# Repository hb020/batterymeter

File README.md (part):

# Handheld Battery Meter on Attiny series 2 <!-- omit in toc -->

This repository is about a "pen size" (handheld) tool for quick measurement of various types of battery resistances/impedances.

This tool uses 2 different methods for measuring impedance values:

- "standard" AC 1 kHz impedance, as used by many.
- Direct Current Impedance Spectroscopy, extracting the bulk (solution) resistance and the SEI (Solid Electrolyte Interphase) resistance, allowing better insight in both battery ageing and battery safety. Normally this would require a lengthy procedure via EIS (Electrochemical Impedance Spectroscopy) and model fitting. This tool allows to do it fast and easy.

## Contents <!-- omit in toc -->

This document handles the reasoning behind the creation of this tool, the methods used, the software and the hardware.

- [Design restrictions](#design-restrictions)
- [Norms and introduction to measurement techniques used](#norms-and-introduction-to-measurement-techniques-used)
- [Battery Equivalent Circuit Model, Spectrum, and the EIS method](#battery-equivalent-circuit-model-spectrum-and-the-eis-method)
  - [Battery Equivalent Circuit Model](#battery-equivalent-circuit-model)
  - [EIS](#eis)
  - [Tools](#tools)
  - [CN0510](#cn0510)
  - [Model fitting](#model-fitting)
  - [Further information](#further-information)
- [Time Domain / DCIS method](#time-domain--dcis-method)
  - [Non-linear behaviour](#non-linear-behaviour)
  - [Pulse timing](#pulse-timing)
  - [Adaptation to other battery layouts or chemistries](#adaptation-to-other-battery-layouts-or-chemistries)
  - [Ratiometric approach](#ratiometric-approach)
  - [Offset cancelling](#offset-cancelling)
  - [Power line Frequency compensation](#power-line-frequency-compensation)
- [Internal Impedance (AC) measurement](#internal-impedance-ac-measurement)
  - [Current levels and test duration](#current-levels-and-test-duration)
  - [Implementation of the sine wave generation](#implementation-of-the-sine-wave-generation)
  - [AC Analysis method](#ac-analysis-method)
  - [ADC sampling considerations](#adc-sampling-considerations)
  - [Ratiometric approach, Offset cancelling, Power line Frequency compensation](#ratiometric-approach-offset-cancelling-power-line-frequency-compensation)
- [Internal Resistance (DC/IR) measurement](#internal-resistance-dcir-measurement)
- [CPU and Software environment](#cpu-and-software-environment)
- [Construction, Connectors, other hardware](#construction-connectors-other-hardware)
  - [Charging](#charging)
- [Buttons](#buttons)
- [Calibration](#calibration)
- [Remote control, SCPI](#remote-control-scpi)
- [Specifications](#specifications)
  - [Voltage](#voltage)
  - [Resistance](#resistance)
- [Repository contents](#repository-contents)
- [Imperfections, TODO's](#imperfections-todos)

---

## Design restrictions

This tool was designed with the following design restrictions:

- handheld, therefore:
  - small
  - limited controls, ideally by 1 finger while measuring
  - "large enough" screen
  - rechargeable
  - no need to cover a large temperature range
- fast measurement
- easy to use
- for use on regular small batteries. No large capacity car batteries or large UPS batteries, and nothing requiring extreme precision. Therefore:
  - at least 0 to 20 Ω, with, and at least 1 mΩ resolution at the lowest range.
  - at least 1V to 16V, and at least 10mV resolution.
  - at least 3 significant digits.
- precision is more important than accuracy. However, 1% accuracy should be attainable on resistance values. Voltage accuracy is of lower priority, as my DMMs can be used for that, and the voltage is less significant in most cases. Therefore:
  - aim for low noise
  - the accuracy of the measuring techniques should depend on as few as possible variables.
  - calibration must be possible.
- USB charging and USB interface
- hand assembly and hand soldering. For me, that means:
  - no BGA or QFN, as I don't have a reflow oven and am too much of a cheapskate to order stencils for the 1 or 2 PCBs I'll make.
  - 0805 components and VSSOP/MSOP 0.5mm pitch are the low limits
  - as a side effect, I can now freely use both sides of the PCB because I don't have to care about warping or components falling off the other side while soldering with hot air.
- using components that I can find in this period of component shortage. This means that sometimes there might be cheaper or better components, they were just not available when I selected them.
- using an Attiny series 2 CPU, because I wanted to try that out and it looked just capable enough. I really would have liked to use the RP2040, but it is not hand solderable enough. Maybe later.
- capable of using the probes that come with the YR1035+, as I also have that tool, and like the connector/probe ease of use/availability. It will also allow me to have easier comparisons.

## Norms and introduction to measurement techniques used

Battery impedance is a complicated subject. A battery does not have <u>one</u> impedance, and even if you get a number, it can mean many things. Also, the battery impedance depends on a lot of different things, like state of charge (SoC), state of health (SoH), temperature, and of course the measurement method. Therefore, various norms exist for measuring the various resistances and impedances of the different battery types. Some of them are:

- IEC 61951-1: NiCd
- IEC 61951-2: NiMH
- IEC 62660-1/2: Li-Ion
- IEC 61960-4: Lithium coin cells

Outside of these norms, various other test methods have arisen lately. Below is an explanation of the different methods I investigated.

---

## Battery Equivalent Circuit Model, Spectrum, and the EIS method

### Battery Equivalent Circuit Model

Various models of battery impedance exist, depending on the chemistry. For Li-Ion cells, the "Combined Randle and Warburg Circuit Model" is often cited as fairly complete, and, with some variations, also applicable to some other chemistries.

*Equivalent circuit model of a Li-Ion battery half-cell system, and nyquist plot of a frequency sweep.*
([source](https://www.jecst.org/upload/pdf/jecst-2019-00528.pdf))

*Nyquist plot, related to Li-Ion cell chemical processes.*
([source](https://www.analog.com/en/design-center/reference-designs/circuits-from-the-lab/CN0510.html))

### EIS

The EIS (Electrochemical Impedance Spectroscopy) method allows one to get a good view of the various components of the battery impedance. With this method an AC load of varying frequency is imposed on the battery, and the voltage swing over the battery is measured. The frequency sweep can go from the millihertz into the megahertz range, and can be used to generate a Nyquist plot like shown above.

Through model fitting, the values of the individual components in the model can than be determined.

For Li-Ion, the values of these components can be used as indicators.

- R<sub>b</sub> (aka R<sub>s</sub> or R<sub>Ω</sub> in other literature) = Bulk (or Solution) resistance. Increases when the battery ages.
- R<sub>SEI</sub> = Solid Electrolyte Interphase resistance. Is an indication of battery safety: it increases for example when the battery has been overcharged.
- R<sub>ct</sub> = Charge Transfer resistance. Increases when the battery is discharged, and when the temperature is lower. At a stable temperature and SoC, it is also a very good indication of battery health.

As an example, experimental results on Li-Ion batteries show that when the battery capacity drops from 3100 mAh to 2600 mAh due to ageing, the value of R<sub>b</sub> rises from 44 mΩ to 51 mΩ, the value of R<sub>SEI</sub> remains between 6 mΩ and 7 mΩ, and the value of R<sub>ct</sub> rises from 6 mΩ to 20 mΩ.

In spite of the insights EIS can give, it has a couple of drawbacks:

- The values are strongly dependent on the battery chemistry and construction details.
- Interpretation can be complicated.
- The data is too complex to show on a small screen.
- A full EIS test generally takes significant time

As a result, this method is very interesting, but unsuited for implementation in a handheld tool.

Fast measurement of full impedance spectra is possible via the use of multi-sine methods, or via time domain methods. More about this later on.

### Tools

Few "small lab" tools exist that support EIS. Examples are the [Biologic Potentiostat](https://www.biologic.net/product_category/potentiostats-galvanostats/), [Hioki IM3590 and BT4560](https://www.hioki.com/download/37483), or the [BK Precision BA8100](https://www.bkprecision.com/products/electrical-battery-testers/BA8100), all costing several thousands of Euros. But one can already get an idea about EIS via the CN0510 circuit, for a significantly lower budget:

### CN0510

An implementation example of a tool is [CN0510 from analog.com](https://www.analog.com/en/design-center/reference-designs/circuits-from-the-lab/CN0510.html). It allows EIS measurements on various types of batteries. Note however that the signal handling board (EVAL-AD5941BATZ), by default, is only usable in the frequency range of about 4Hz - 5Khz. Outside of that, the accuracy is degraded, and below 1Hz, the noise of the input circuitry gets quite noticeable (1/f noise). With the following minor modifications, 0.5Hz - 5kHz can be made possible though:

- add U4 (otherwise the first couple of seconds of measurements are totally off)
- change C5, C6, C36, C37, C38, C39 from 2.2uF to 10uF.
- change R18, R19, R2, R3, R4, R5 from 2Meg to 10Meg.

### Model fitting

For the impedance analysis and the model fitting, several software packages exist, like [ZView](https://www.scribner.com/software/) or [impedance.py](https://github.com/ECSHackWeek/impedance.py). See the [/EISMeasurements](/EISMeasurements) directory in this repository for some fitting tests with both of these tools.

### Further information

For more information on EIS and alternative methods, see for example <https://www.gamry.com/application-notes/EIS/basics-of-electrochemical-impedance-spectroscopy/> or <https://doi.org/10.1016/j.jpowsour.2020.228742>.

Note that EIS is used in a lot of fields, not only for batteries. However, research on batteries has gotten a significant boost lately with the widespread arrival of electric cars.

---

## Time Domain / DCIS method

As mentioned above, EIS frequency domain analysis is not only complicated, but also lengthy. Time domain analysis methods have come up lately that allow acceptable approximations to the results that can be obtained via EIS. One of the approaches is called DCIS (Direct Current Impedance Spectroscopy), which is described here: <https://www.mdpi.com/1996-1073/14/15/4396/htm>

The idea behind DCIS (and other time domain methods) is that when one exposes the battery to current pulses, the voltage relaxation times give away details of the different RC components in the battery model. Care must be taken to exclude non linear behaviour and to tune the current pulses in such a way that the correct components can be derived easily.

### Non-linear behaviour

One key phrase:

> In the battery model, when the polarization potential change |∆ϕ| caused by an external signal is less than 10 mV and the signal time is short enough, the effect of concentration polarization (Zd in battery model) can be ignored.

I therefore need to keep the test currents low, and the pulses short. Both requirements perfectly fit my tool's design requirements.

### Pulse timing

In regular Li-Ion batteries, the various components show at various frequencies:

- R<sub>b</sub>: > 1kHz
- R<sub>SEI</sub> (and CPE<sub>SEI</sub>): > 1Hz, < 1kHz
- R<sub>ct</sub> (and CPE<sub>electrode</sub> and W): < 1Hz

The approach is that for every individual component, 1 specific timed constant current pulse will be used. The width of the pulse is about 5 * RC time of the component. That gives:

- for R<sub>b</sub>: T<sub>1</sub> = 0.25ms
- for R<sub>SEI</sub>: T<sub>2</sub> = 10ms
- for R<sub>ct</sub>: T<sub>3</sub> = 400ms

The pulses are spaced out by a small relaxation time. The voltage drop over the battery is measured at the end of each current pulse, and the battery resistance at that point in time is calculated:

- for T<sub>1</sub>: V<sub>drop</sub> / I<sub>pulse</sub> = R<sub>b</sub>
- for T<sub>2</sub>: V<sub>drop</sub> / I<sub>pulse</sub> = R<sub>b</sub> + R<sub>SEI</sub>
- for T<sub>3</sub>: V<sub>drop</sub> / I<sub>pulse</sub> = R<sub>b</sub> + R<sub>SEI</sub> + R<sub>ct</sub>

Unfortunately, I will want to do multiple measurements to drown out noise and do power line frequency compensation. That makes T<sub>3</sub> unsuited for my tool, and I must limit myself to  R<sub>b</sub> and R<sub>SEI</sub>.

### Adaptation to other battery layouts or chemistries

The timings mentioned above are suitable for your average Li-Ion 18650 cell. If you want to use the DCIS method on other battery layouts or chemistries, you can adapt the timings via SCPI commands (see `CAL:T(1|2|PAUSE) {uint16}` below).

### Ratiometric approach

The current pulse is sent through the battery, that is placed in series with a known resistor.
The battery resistance is deducted from the relation between the voltage fluctuation over the known resistor and the voltage fluctuation over the battery. Hence, there is no need for a known current source, nor a known voltage reference.

With U<sub>batt</sub> as the voltage drop over the battery, U<sub>ref</sub> the voltage over the reference resistor, and R<sub>ref</sub> the reference resistor: R<sub>batt</sub> = R<sub>ref</sub> * (U<sub>batt</sub>/U<sub>ref</sub>).

Since U<sub>batt</sub> and U<sub>ref</sub> are so small, they are amplified by an AC coupled low noise instrumentation amplifier. The output signal is fed into the differential ADC of the processor. In order to avoid amplification differences and other signal path differences, multiplexing via a common measurement circuit is used. An input switch allows switching between the battery and the reference resistor.

The frequency cut-off point of the high-pass filter at the input of the instrumentation amplifier is well below the frequencies used in the measurements.

### Offset cancelling

The (potentially large) DC offset at the entry of the circuit is cancelled at the start of the measurements, by a low impedance short of the signal to VCC/2. The short is applied for as long is needed, and stopped when the processor sees a close to 0V differential signal on the ADC.

### Power line Frequency compensation

In order to reduce the noise and the influence of the power line frequency, multiple samples are taken, and the results are averaged. The timing of the samples is adapted to the configured power line frequency: an identical number of samples is taken for each opposing polarity of the power line signal.

The software allows setting of the power line frequency (50 or 60) via SCPI commands.

---

## Internal Impedance (AC) measurement

This is the industry standard AC 1kHz test. A small 1kHz current (ideally sine wave) is applied to the battery, and the AC voltage at the battery is measured. The impedance is then deducted from the current and the voltage.
This method is widespread, low power, and fast, so I can include it in my tool.

### Current levels and test duration

The maximum voltage swing allowed depends on the battery type, as above certain levels, the values would be skewed by other factors. For NiCd, that limit is about 20mV, and for Lithium chemistries, 10mV seems to be indicated. As a result, I do not set a test specific current, but adapt the test current to the selected range.

The "correct" duration of the test varies. EC 61951-1 for example states that the test duration must be 1 to 5 seconds, but that is not handy for fast manual use. A test duration of 100ms suffices normally.

### Implementation of the sine wave generation

The CPU I chose does not have a sine wave generator. It does have PWM, but making a sine wave with that was hard to do while running the ADC. As a result, I generate a 1kHz square wave on CPU, and do the transformation to a sine wave with an analog phase-shift circuit. That signal is then, after some amplification and level shifting, fed into a voltage controlled current sink.

### AC Analysis method

Instead of a full fledged FFT/DFT, Goertzel's Algorithm is used. It is essentially a mathematical bandpass filter that gives a magnitude (and phase) reading. It is especially suited as I generate the 1kHz tone myself and can sync the ADC sampling to that tone generation. As a result, it is very light on resources: I can do the calculations while sampling, and do not need large memory buffers.

About the configuration of Goertzel:

- nr_of_samples (N) should be as high as possible:
  - sample_rate/N is bin width.
  - more samples therefore gives more noise suppression
- Target frequencies must be integer multiples of sample_rate/N

Some of the inspirations:

- <https://www.embedded.com/the-goertzel-algorithm/>
- <https://fr.mathworks.com/matlabcentral/answers/?language=fr%2Cen&search_origin=ans_browse&term=goertzel>

### ADC sampling considerations

The CPU having limited RAM, I prefer to do the tone generation, ADC sampling and AC analysis all in sync, run-time. I do not sample and analyse later, as that would take too much RAM. It also gives me the possibility to make the sampling as long as I want, increasing noise suppression. It however requires an optimised ADC loop, so I go outside of megaTinyCore's analogRead() function.

As I have low noise pre-amps, I do not use the PGA: I set gain 0.

The trigger generator is TCA0, the most capable of the timers on the CPU, and I trigger the ADC sampling via the Event system (ADC_START_EVENT_TRIGGER_gc and USERADC0START). During sampling, I generate the 1kHz square wave in code, and do the Goertzel calculations.
Tests have shown that at a 10kHz trigger signal, I have about 20us CPU time left per sample. 12kHz would not be possible, unless I raise the ADC clock rate. Maybe also CCL could help, but I haven't looked.

Interrupts are only used for error conditions on the ADC. Other interrupt sources, like the time library, are disabled, as it would provoke jitter or overruns.

As this is time critical code, debugging support is available in code, via USEREVSYSEVOUTC for example.

I do not use tone(), as that is interrupt driven.

### Ratiometric approach, Offset cancelling, Power line Frequency compensation

A sine wave of 1 kHz is sent through the battery, that is placed in series with a known resistor.
The battery resistance is deducted from the relation between the AC voltage over the known resistor and the AC voltage over the battery. Hence, there is no need for a known current source, nor a known voltage reference.

For more details, see the chapter on "Ratiometric approach" in the description of the DCIS method.

Also here, DC offset cancelling and power line frequency compensation is used. See the related chapters in the description of the DCIS method.

---

## Internal Resistance (DC/IR) measurement

This method is frequently encountered, because it is very simple. It is in essence a DC measurement technique.

> The cell shall be discharged at a constant current of value I<sub>1</sub>. At the end of a discharge period of T<sub>1</sub> s, the voltage U<sub>1</sub> during discharge shall be measured and recorded. The discharge current shall then be immediately increased to a constant value of I<sub>2</sub>, and the corresponding voltage U<sub>2</sub> during discharge shall be measured and recorded again at the end of a discharge period of T<sub>2</sub> s.

Therefore: R<sub>dc</sub> = (U<sub>1</sub> - U<sub>2</sub>)/(I<sub>2</sub> - I<sub>1</sub>)

The currents I<sub>1</sub> and I<sub>2</sub>, and the times T<sub>1</sub> and T<sub>2</sub> depend on the type and capacity of the battery. Example: For NiCd, I<sub>1</sub> is normally between 0.2 and 1 times the C value in Amps, I<sub>2</sub> = 10 * I<sub>1</sub>, T<sub>1</sub> = 10, T<sub>2</sub> = 3. For Lead Acid batteries, the currents can become even larger.

Those large currents, and the accompanying dissipation, make it unsuited for integration in a small handheld tool. Also, because this is such a crude method, abstracting most of the battery model, I am not using this method.

---

## CPU and Software environment

- Arduino IDE (unfortunately. platformIO was not very mature at the time of creation: board support had just arrived.)
- megaTinyCore
- CPU: Attiny 3266-SU (SOIC300, non automotive, 32kB Flash, 3kB RAM, 256B EEPROM)
- Display (SSD1306) via Tiny4kOLED (not SSD1306_minimal, as that is less maintained)
- SparkFun_PCA9536_Arduino_Library
- a modified and local version of vrekrer's scpi_parser

Please note that the flash memory is close to the limit: it is 97% full.

## Construction, Connectors, other hardware

The case chosen is a Hammond 1593DBK. That case comes with flat and curved front/back panels. Use the flat one for the back.

The nose cone is 3D printed, see the [nose cone STEP file](/freecad/noseCone.STEP). The holes for the pins may be too small, I had to drill them out.

The pogo pins in the nose cone are regular R100-1W sockets, with P100-B1 pogo pins. For images and dimensions, see the `pogo-*` files in the [/img](/img) folder.

The probe connector at the back is a "avionics" XS10 4P male connector, the same as on the YR1035+. This connector accepts regular YR1035+ compatible 4W probes, or in conjunction with the nose pogo pins, a custom made - probe (just half of the regular 4W probe). The nose pogo pins are directly connected to the + pins on the XS10 connector. As a result, one can also connect a 4W rig:

The serial connector/charge plug is a USB micro B. I should have chosen USB-C, but I still had a lot of USB micro B connectors.

The navigation switch is a SLLB510100 from Alps Alpine. You probably need some glue to fix it on the PCB, as the "fixing" tabs on the side are very/too small.

The reference resistors are all used in a 4W (kelvin) setup, either through the use of 4W resistors, or in a "poor man's" way, via the PCB layout:

.

All components on the board are specified in the kicad files. The choice of components is, as can be expected, influenced by the component shortage during 2021-2022.

The input circuitry is protected against reverse polarity and moderate overvoltage.

### Charging

If a rechargeable battery is used, the USB charges the battery via trickle charging at about 0.05C for your average 850mAh NiMh AAA battery. This charge current is so little that charging while ON is not possible. Therefore: Charge while OFF.

## Buttons

ON: short press button at the back.

OFF: long press button at the back, or via software control.

Switch between AC and DCIS measurement, or leave remote control: press the navigation switch.

Change range: via left/right of the navigation switch. The 'Auto' range is at both ends.

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
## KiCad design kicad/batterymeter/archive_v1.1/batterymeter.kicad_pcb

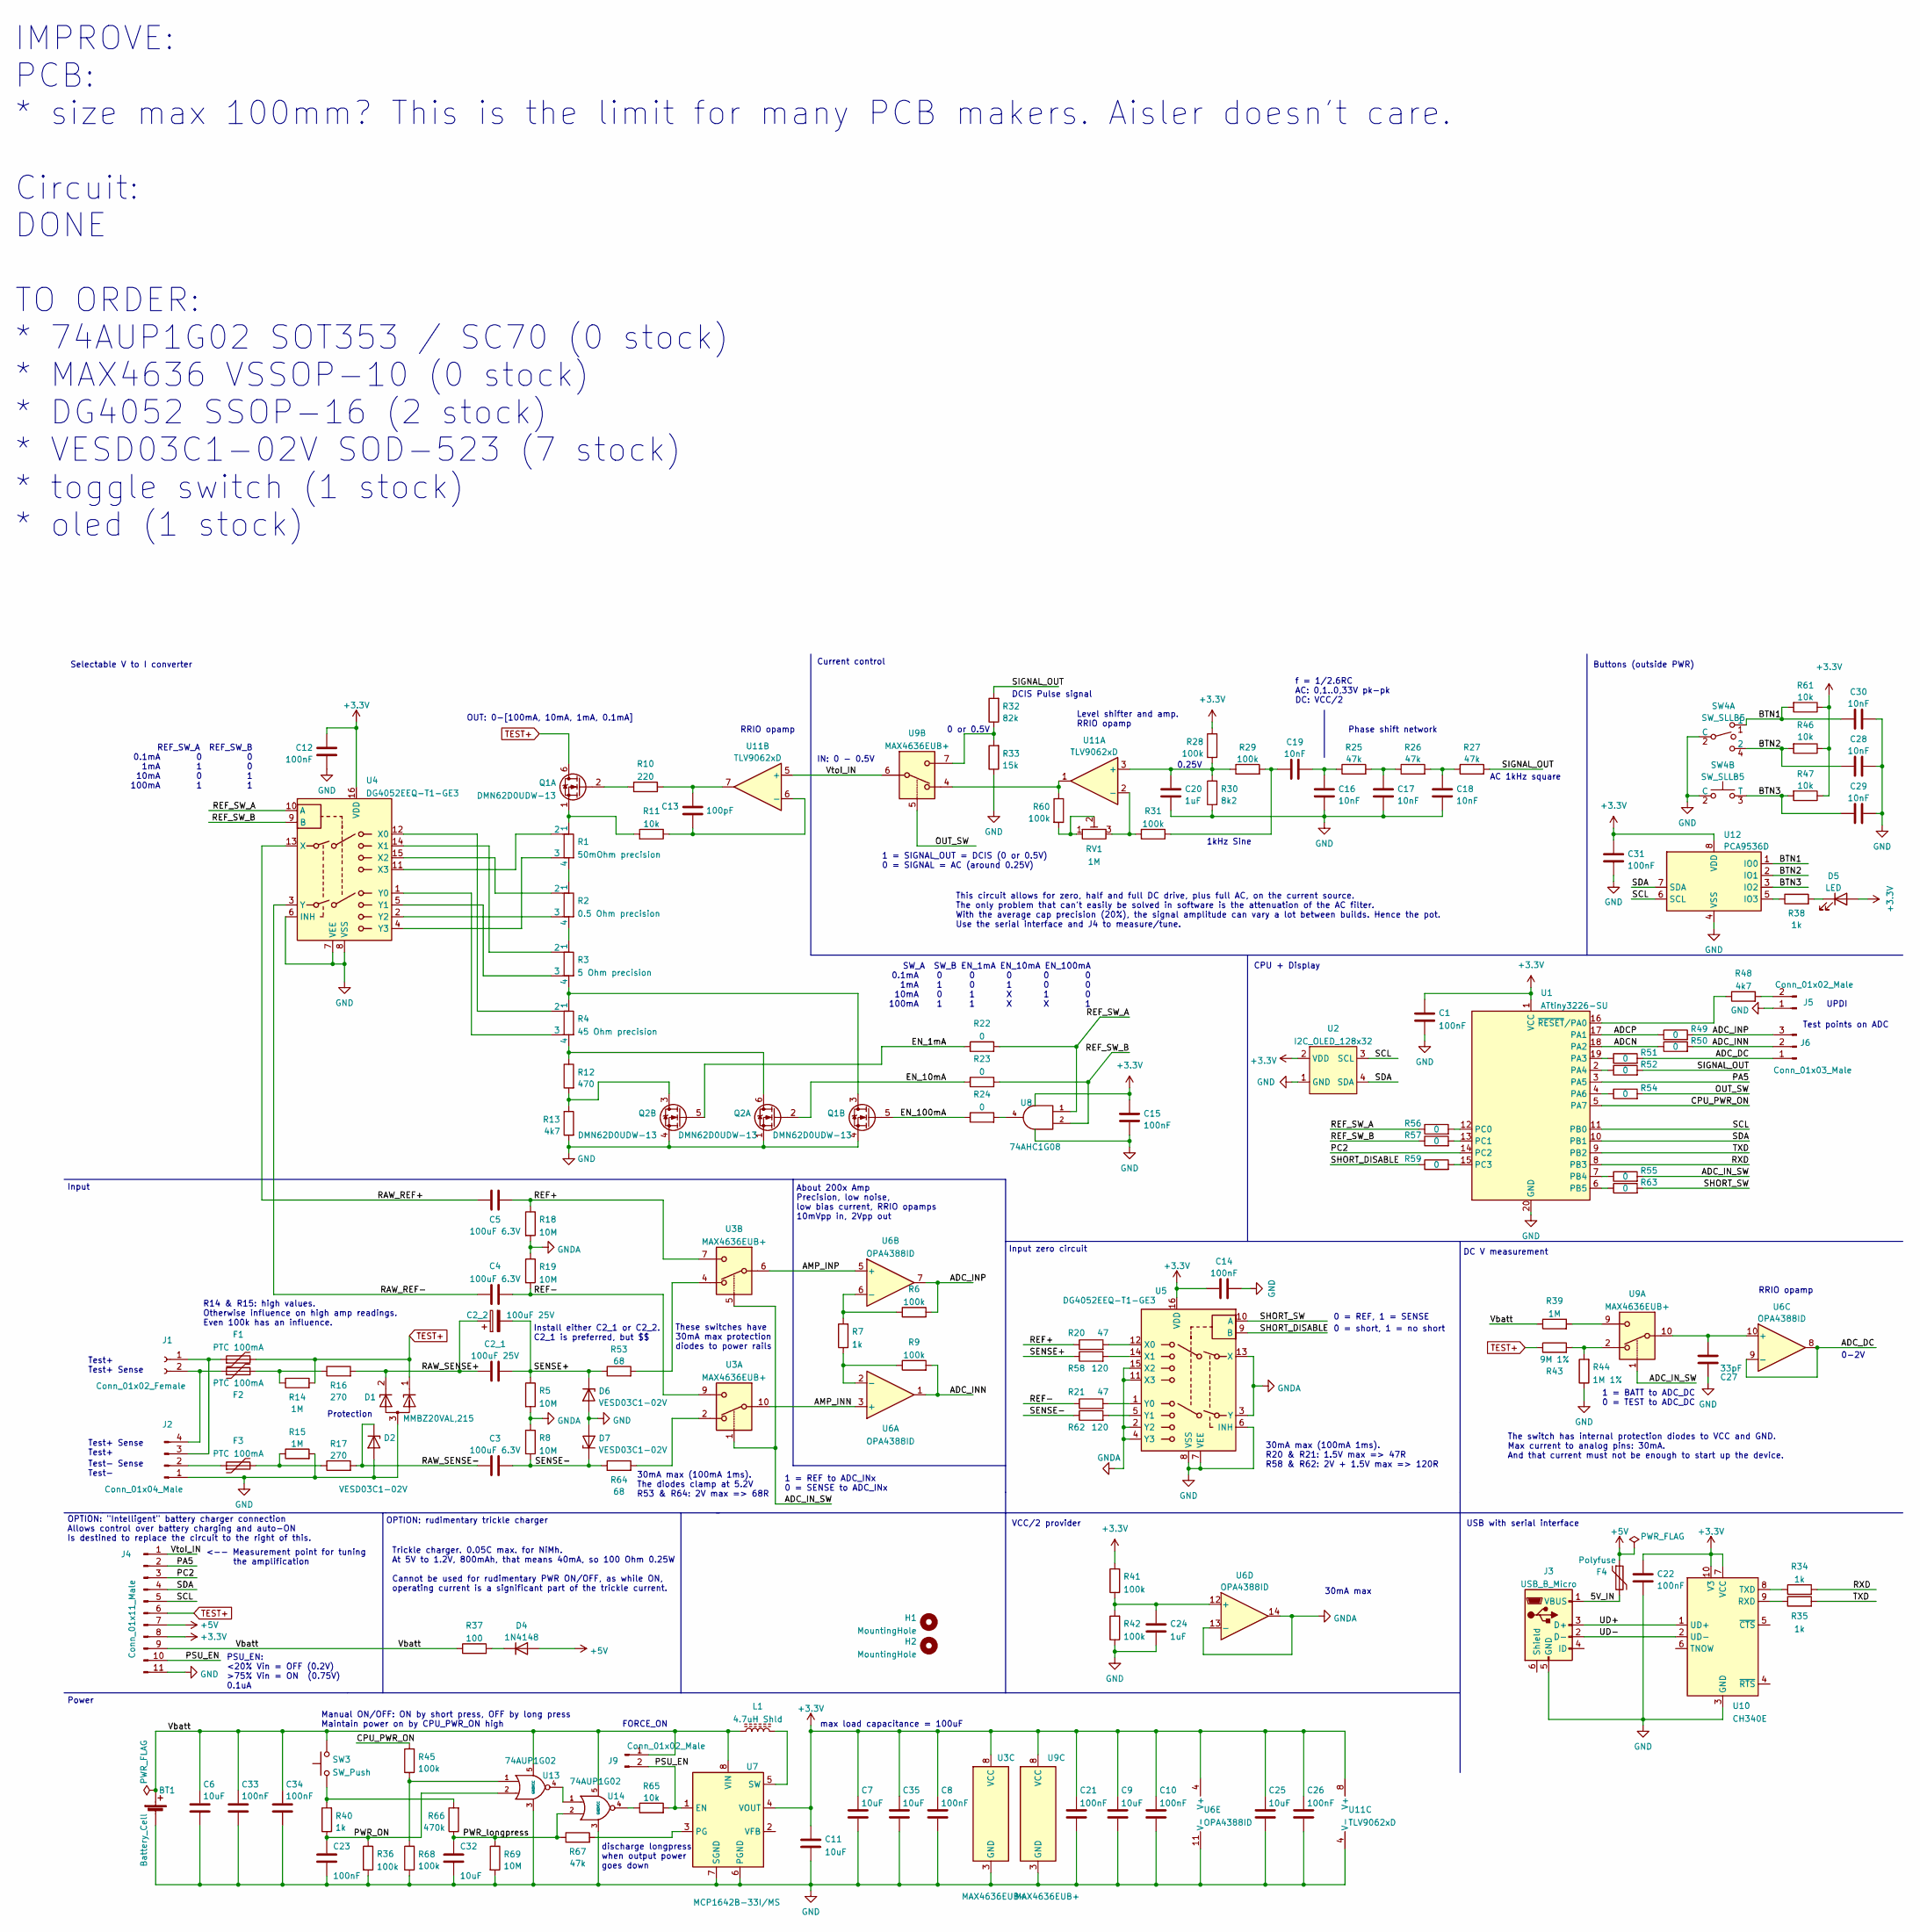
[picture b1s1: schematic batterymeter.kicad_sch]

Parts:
BT1: Battery_Cell; BatteryHolder_Keystone_2466_1xAAA
C1, C8, C10, C12, C14, C15, C21, C22, C23, C26, C31, C33, C34: 100nF; C_0805_2012Metric_Pad1.18x1.45mm_HandSolder
C2_1: 100uF 25V; KCM55WC71E107MH13
C2_2: 100uF 25V; CP_Elec_6.3x7.7
C3, C4, C5: 100uF 6.3V; C_1206_3216Metric_Pad1.33x1.80mm_HandSolder
C6, C7, C9, C11, C25, C32, C35: 10uF; C_0805_2012Metric_Pad1.18x1.45mm_HandSolder
C13: 100pF; C_0805_2012Metric_Pad1.18x1.45mm_HandSolder
C16, C17, C18, C19, C28, C29, C30: 10nF; C_0805_2012Metric_Pad1.18x1.45mm_HandSolder
C20, C24: 1uF; C_0805_2012Metric_Pad1.18x1.45mm_HandSolder
C27: 33pF; C_0805_2012Metric_Pad1.18x1.45mm_HandSolder
D1: MMBZ20VAL,215; SOT-23
D2, D6, D7: VESD03C1-02V; D_SOD-523
D4: 1N4148; D_SOD-123
D5: LED; LED_1206_3216Metric_Pad1.42x1.75mm_HandSolder
F1, F2, F3: PTC 100mA; Fuse_1206_3216Metric_Pad1.42x1.75mm_HandSolder
F4: Polyfuse; Fuse_1206_3216Metric_Pad1.42x1.75mm_HandSolder
H1, H2: MountingHole; MountingHole_3.2mm_M3_ISO14580
J1: Conn_01x02_Female; PinSocket_1x02_P2.54mm_Horizontal
J2: Conn_01x04_Male; JST_XH_B4B-XH-A_1x04_P2.50mm_Vertical
J3: USB_B_Micro; USB_Micro-B_mine
J4: Conn_01x11_Male; PinHeader_1x11_P2.54mm_Vertical
J5, J9: Conn_01x02_Male; PinHeader_1x02_P2.54mm_Vertical
J6: Conn_01x03_Male; PinHeader_1x03_P2.54mm_Vertical
L1: 4.7uH Shld; L_Coilcraft_LPS4018
Q1, Q2: DMN62D0UDW-13; SOT-363_SC-70-6
R1: 50mOhm precision; R_Shunt_Ohmite_LVK12_ALT
R2: 0.5 Ohm precision; R_1206_3216Metric_4Wire
R3: 5 Ohm precision; R_1206_3216Metric_4Wire
R4: 45 Ohm precision; R_1206_3216Metric_4Wire
R5, R8, R18, R19, R69: 10M; R_0805_2012Metric_Pad1.20x1.40mm_HandSolder
R6, R9, R28, R29, R31, R36, R41, R42, R45, R60, R68: 100k; R_0805_2012Metric_Pad1.20x1.40mm_HandSolder
R7, R34, R35, R38, R40: 1k; R_0805_2012Metric_Pad1.20x1.40mm_HandSolder
R10: 220; R_0805_2012Metric_Pad1.20x1.40mm_HandSolder
R11, R46, R47, R61, R65: 10k; R_0805_2012Metric_Pad1.20x1.40mm_HandSolder
R12: 470; R_0805_2012Metric_Pad1.20x1.40mm_HandSolder
R13, R48: 4k7; R_0805_2012Metric_Pad1.20x1.40mm_HandSolder
R14, R15, R39: 1M; R_0805_2012Metric_Pad1.20x1.40mm_HandSolder
R16, R17: 270; R_0805_2012Metric_Pad1.20x1.40mm_HandSolder
R20, R21: 47; R_0805_2012Metric_Pad1.20x1.40mm_HandSolder
R22, R23, R24, R49, R50, R51, R52, R54, R55, R56, R57, R59, R63: 0; R_0805_2012Metric_Pad1.20x1.40mm_HandSolder
R25, R26, R27, R67: 47k; R_0805_2012Metric_Pad1.20x1.40mm_HandSolder
R30: 8k2; R_0805_2012Metric_Pad1.20x1.40mm_HandSolder
R32: 82k; R_0805_2012Metric_Pad1.20x1.40mm_HandSolder
R33: 15k; R_0805_2012Metric_Pad1.20x1.40mm_HandSolder
R37: 100; R_1206_3216Metric_Pad1.30x1.75mm_HandSolder
R43: 9M 1%; R_0805_2012Metric_Pad1.20x1.40mm_HandSolder
R44: 1M 1%; R_0805_2012Metric_Pad1.20x1.40mm_HandSolder
R53, R64: 68; R_0805_2012Metric_Pad1.20x1.40mm_HandSolder
R58, R62: 120; R_0805_2012Metric_Pad1.20x1.40mm_HandSolder
R66: 470k; R_0805_2012Metric_Pad1.20x1.40mm_HandSolder
RV1: 1M; Potentiometer_Bourns_3266Y_Vertical
SW3: SW_Push; SW_Tactile_SPST_Angled_PTS645Vx83-2LFS
SW4: SW_SLLB5; SW_SLLB510100
U1: ATtiny3226-SU; SOIC-20W_7.5x12.8mm_P1.27mm
U2: I2C_OLED_128x32
U3, U9: MAX4636EUB+; VSSOP-10_3x3mm_P0.5mm
U4, U5: DG4052EEQ-T1-GE3; TSSOP-16_4.4x5mm_P0.65mm
U6: OPA4388ID; SOIC-14_3.9x8.7mm_P1.27mm
U7: MCP1642B-33I/MS; MSOP-8_3x3mm_P0.65mm
U8: 74AHC1G08; SOT-23-5_HandSoldering
U10: CH340E; MSOP-10_3x3mm_P0.5mm
U11: TLV9062xD; VSSOP-8_3.0x3.0mm_P0.65mm
U12: PCA9536D; SOIC-8_3.9x4.9mm_P1.27mm
U13, U14: 74AUP1G02; SOT-353_SC-70-5_Handsoldering

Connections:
+3V3: C1.1, C7.1, C8.1, C9.1, C10.1, C11.1, C12.1, C14.1, C15.1, C21.1, C22.1, C25.1, C26.1, C31.1, C35.1, D5.2 (A), J4.8, R28.2, R41.2, R46.1, R47.1, R61.1, U1.1 (VCC), U2.2 (VDD), U3.8 (VCC), U4.16 (VDD), U5.16 (VDD), U6.4 (V+), U7.4 (VOUT), U8.5 (VCC), U9.8 (VCC), U10.7 (VCC), U10.10 (V3), U11.8 (V+), U12.8 (VDD)
+5V: D4.2 (A), F4.1, J4.7
/5V_IN: F4.2, J3.1 (VBUS)
/ADCN: R50.1, U1.18 (PA2)
/ADCP: R49.1, U1.17 (PA1)
/ADC_DC: J6.1, R51.2, U6.8, U6.9 (-)
/ADC_INN: J6.2, R9.2, R50.2, U6.1
/ADC_INP: J6.3, R6.2, R49.2, U6.7
/ADC_IN_SW: R55.2, U3.1, U3.5, U9.1
/AMP_INN: U3.10, U6.3 (+)
/AMP_INP: U3.6, U6.5 (+)
/BTN1: C30.1, R61.2, SW4.1, U12.1 (IO0)
/BTN2: C28.1, R46.2, SW4.4 (2), U12.2 (IO1)
/BTN3: C29.1, R47.2, SW4.3 (T), U12.3 (IO2)
/CPU_PWR_ON: R45.2, U1.5 (PA7)
/EN_1mA: Q2.5 (G), R22.1
/EN_10mA: Q2.2 (G), R23.1
/EN_100mA: Q1.5 (G), R24.1
/OUT_SW: R54.2, U9.5
/PA5: J4.2, U1.3 (PA5)
/PC2: J4.3, U1.14 (PC2)
/PSU_EN: J4.10, J9.2, R65.2, U7.1 (EN)
/PWR_ON: C23.1, R36.1, R40.1, U13.2
/PWR_longpress: C32.1, R66.1, R67.1, R69.1, U14.2
/RAW_REF+: C5.1, U4.13 (X)
/RAW_REF-: C4.1, U4.3 (Y)
/RAW_SENSE+: C2_1.1, C2_2.1, D1.2 (K), R16.2
/RAW_SENSE-: C3.1, D2.1 (K), R17.2
/REF+: C5.2, R18.1, R20.1, U3.7
/REF-: C4.2, R19.2, R21.1, U3.9
/REF_SW_A: R22.2, R56.1, U4.10 (A), U8.1
/REF_SW_B: R23.2, R57.1, U4.9 (B), U8.2
/RXD: R34.2, U1.8 (PB3)
/SCL: J4.5, U1.11 (PB0), U2.3 (SCL), U12.6 (SCL)
/SDA: J4.4, U1.10 (PB1), U2.4 (SDA), U12.7 (SDA)
/SENSE+: C2_1.2, C2_2.2, D6.1 (K), R5.1, R53.1, R58.1
/SENSE-: C3.2, D7.1 (K), R8.2, R62.1, R64.1
/SHORT_DISABLE: R59.1, U5.9 (B)
/SHORT_SW: R63.2, U5.10 (A)
/SIGNAL_OUT: R27.2, R32.2, R52.2
/TXD: R35.2, U1.9 (PB2)
/UD+: J3.3 (D+), U10.1 (UD+)
/UD-: J3.2 (D-), U10.2 (UD-)
/Vbatt: BT1.1 (+), C6.1, C33.1, C34.1, J4.9, J9.1, L1.1, R37.1, R39.1, SW3.2, U7.8 (VIN), U13.5 (VCC), U14.5 (VCC)
/VtoI_IN: J4.1, U9.6, U11.5 (+)
GND: BT1.2 (-), C1.2, C6.2, C7.2, C8.2, C9.2, C10.2, C11.2, C12.2, C14.2, C15.2, C16.2, C17.2, C18.2, C20.1, C21.2, C22.2, C23.2, C24.2, C25.2, C26.2, C27.2, C28.2, C29.2, C30.2, C31.2, C32.2, C33.2, C34.2, C35.2, D1.3 (A), D2.2 (A), D6.2 (A), D7.2 (A), J2.1, J3.5 (GND), J4.11, J5.1, Q1.4 (S), Q2.1 (S), Q2.4 (S), R13.2, R15.2, R30.1, R33.1, R36.2, R42.1, R44.1, R68.1, R69.2, SW4.2 (C), U1.20 (GND), U2.1 (GND), U3.3 (GND), U4.6 (INH), U4.7 (VEE), U4.8 (VSS), U5.6 (INH), U5.7 (VEE), U5.8 (VSS), U6.11 (V-), U7.6 (PGND), U7.7 (SGND), U8.3 (GND), U9.3 (GND), U10.3 (GND), U11.4 (V-), U12.4 (VSS), U13.3 (GND), U14.3 (GND)
GNDA: R5.2, R8.1, R18.2, R19.1, U5.2 (Y2), U5.3 (Y), U5.4 (Y3), U5.11 (X3), U5.13 (X), U5.15 (X2), U6.13 (-), U6.14
unnamed: C13.1, R11.1, U11.6 (-)
unnamed: C13.2, R10.1, U11.7
unnamed: C16.1, C19.2, R25.1
unnamed: C17.1, R25.2, R26.1
unnamed: C18.1, R26.2, R27.1
unnamed: C19.1, R29.2, R31.1
unnamed: C20.2, R28.1, R29.1, R30.2, U11.3 (+)
unnamed: C24.1, R41.1, R42.2, U6.12 (+)
unnamed: C27.1, U6.10 (+), U9.10
unnamed: D4.1 (K), R37.2
unnamed: D5.1 (K), R38.2
unnamed: F1.1, J1.1, J2.3
unnamed: F2.1, J1.2, J2.4
unnamed: F2.2, R14.1, R16.1
unnamed: F3.1, J2.2
unnamed: F3.2, R15.1, R17.1
unnamed: J5.2, R48.2
unnamed: L1.2, U7.5 (SW)
unnamed: Q1.1 (S), R1.1, R11.2
unnamed: Q1.2 (G), R10.2
unnamed: Q1.3 (D), R3.4, R4.1
unnamed: Q2.3 (D), R12.2, R13.1
unnamed: Q2.6 (D), R4.4, R12.1
unnamed: R1.2, U4.11 (X3)
unnamed: R1.3, U4.4 (Y3)
unnamed: R1.4, R2.1
unnamed: R2.2, U4.15 (X2)
unnamed: R2.3, U4.2 (Y2)
unnamed: R2.4, R3.1
unnamed: R3.2, U4.14 (X1)
unnamed: R3.3, U4.5 (Y1)
unnamed: R4.2, U4.12 (X0)
unnamed: R4.3, U4.1 (Y0)
unnamed: R6.1, R7.2, U6.6 (-)
unnamed: R7.1, R9.1, U6.2 (-)
unnamed: R20.2, U5.12 (X0)
unnamed: R21.2, U5.1 (Y0)
unnamed: R24.2, U8.4
unnamed: R31.2, RV1.3, U11.2 (-)
unnamed: R32.1, R33.2, U9.7
unnamed: R34.1, U10.8 (TXD)
unnamed: R35.1, U10.9 (RXD)
unnamed: R38.1, U12.5 (IO3)
unnamed: R39.2, U9.9
unnamed: R40.2, R66.2, SW3.1
unnamed: R43.2, R44.2, U9.2
unnamed: R45.1, R68.2, U13.1
unnamed: R48.1, U1.16 (~RESET/PA0)
unnamed: R51.1, U1.19 (PA3)
unnamed: R52.1, U1.2 (PA4)
unnamed: R53.2, U3.4
unnamed: R54.1, U1.4 (PA6)
unnamed: R55.1, U1.7 (PB4)
unnamed: R56.2, U1.12 (PC0)
unnamed: R57.2, U1.13 (PC1)
unnamed: R58.2, U5.14 (X1)
unnamed: R59.2, U1.15 (PC3)
unnamed: R60.1, U9.4, U11.1
unnamed: R60.2, RV1.1, RV1.2
unnamed: R62.2, U5.5 (Y1)
unnamed: R63.1, U1.6 (PB5)
unnamed: R64.2, U3.2
unnamed: R65.1, U14.4
unnamed: R67.2, U7.3 (PG)
unnamed: U13.4, U14.1
TEST+: D1.1 (K), F1.2, J4.6, Q1.6 (D), R14.2, R43.1

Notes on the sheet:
Power
30mA max (100mA 1ms). R20 & R21: 1.5V max => 47R R58 & R62: 2V + 1.5V max => 120R
0-2V
30mA max
0 = REF, 1 = SENSE
Protection
The switch has internal protection diodes to VCC and GND. Max current to analog pins: 30mA. And that current must not be enough to start up the device.
Test+ Test+ Sense
1 = REF to ADC_INx 0 = SENSE to ADC_INx
1 = BATT to ADC_DC 0 = TEST to ADC_DC
R14 & R15: high values. Otherwise influence on high amp readings. Even 100k has an influence.
0 or 0.5V
IMPROVE: PCB: * size max 100mm? This is the limit for many PCB makers. Aisler doesn't care. Circuit: DONE TO ORDER: * 74AUP1G02 SOT353 / SC70 (0 stock) * MAX4636 VSSOP-10 (0 stock) * DG4052 SSOP-16 (2 stock) * VESD03C1-02V SOD-523 (7 stock) * toggle switch (1 stock) * oled (1 stock)
Manual ON/OFF: ON by short press, OFF by long press Maintain power on by CPU_PWR_ON high
Buttons (outside PWR)
About 200x Amp Precision, low noise, low bias current, RRIO opamps 10mVpp in, 2Vpp out
OPTION: rudimentary trickle charger
0.25V
This circuit allows for zero, half and full DC drive, plus full AC, on the current source. The only problem that can't easily be solved in software is the attenuation of the AC filter. With the average cap precision (20%), the signal amplitude can vary a lot between builds. Hence the pot. Use the s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
DC V measurement
OPTION: "Intelligent" battery charger connection Allows control over battery charging and auto-ON Is destined to replace the circuit to the right of this.
Selectable V to I converter
Test+ Sense Test+
1kHz Sine
30mA max (100mA 1ms). The diodes clamp at 5.2V R53 & R64: 2V max => 68R
Test points on ADC
DCIS Pulse signal
max load capacitance = 100uF
RRIO opamp
OUT: 0-[100mA, 10mA, 1mA, 0.1mA]
AC 1kHz square
discharge longpress when output power goes down
Phase shift network
Install either C2_1 or C2_2. C2_1 is preferred, but $$
USB with serial interface
VCC/2 provider
PSU_EN: <20% Vin = OFF (0.2V) >75% Vin = ON (0.75V) 0.1uA
CPU + Display
Test- Sense Test-
REF_SW_A REF_SW_B 0.1mA 0 0 1mA 1 0 10mA 0 1 100mA 1 1

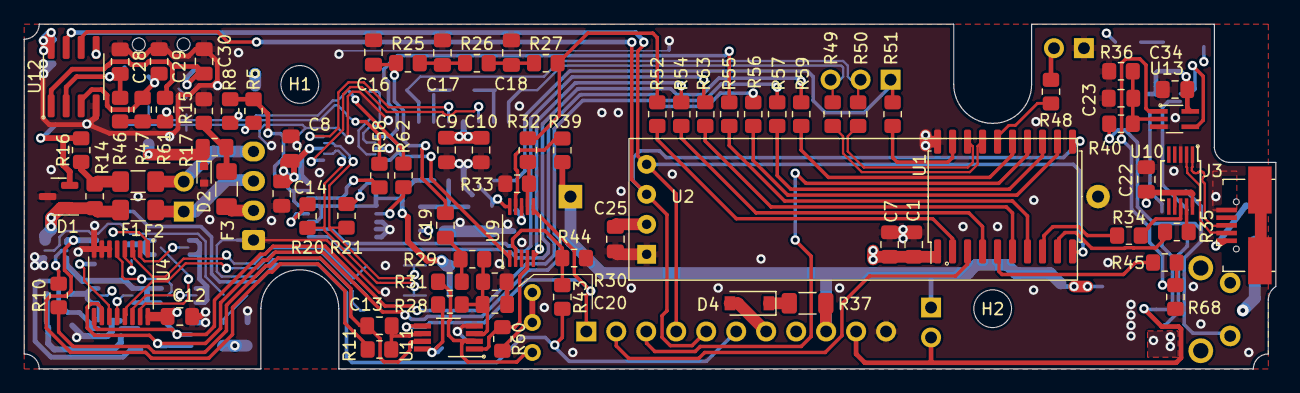
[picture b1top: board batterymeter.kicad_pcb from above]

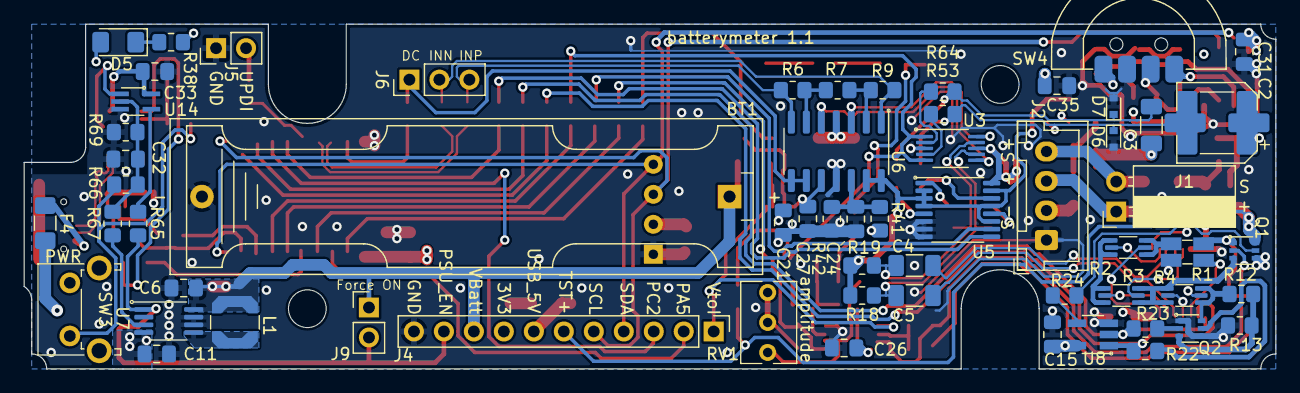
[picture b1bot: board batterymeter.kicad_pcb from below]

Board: 4 copper layers, 106.0 x 29.2 mm, 145 parts (62 on the bottom side), 113 nets.

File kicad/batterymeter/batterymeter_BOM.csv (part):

"Source:","/Users/hboot/Documents/personal/bricolage/HomeProjects/batterymeter/kicad/batterymeter/batterymeter.kicad_sch"
"Date:","2023 January 08, Sunday 09:40:47"
"Tool:","Eeschema (6.0.10-0)"
"Generator:","/Applications/KiCad/KiCad.app/Contents/SharedSupport/plugins/bom_csv_grouped_by_value.py"
"Component Count:","143"

"Individual Components:"

"Item","Qty","Reference(s)","Value","LibPart","Footprint","Datasheet"
"","","BT1","Battery_Cell","Device:Battery_Cell","Battery:BatteryHolder_Keystone_2466_1xAAA","~"
"","","C1","100nF","Device:C","Capacitor_SMD:C_0805_2012Metric_Pad1.18x1.45mm_HandSolder","~"
"","","C2","100uF 25V","Device:C","mylib:KCM55WC71E107MH13","~"
"","","C3","100uF 6.3V","Device:C","Capacitor_SMD:C_1206_3216Metric_Pad1.33x1.80mm_HandSolder","~"
"","","C4","100uF 6.3V","Device:C","Capacitor_SMD:C_1206_3216Metric_Pad1.33x1.80mm_HandSolder","~"
"","","C5","100uF 6.3V","Device:C","Capacitor_SMD:C_1206_3216Metric_Pad1.33x1.80mm_HandSolder","~"
"","","C6","10uF","Device:C","Capacitor_SMD:C_0805_2012Metric_Pad1.18x1.45mm_HandSolder","~"
"","","C7","10uF","Device:C","Capacitor_SMD:C_0805_2012Metric_Pad1.18x1.45mm_HandSolder","~"
"","","C8","100nF","Device:C","Capacitor_SMD:C_0805_2012Metric_Pad1.18x1.45mm_HandSolder","~"
"","","C9","10uF","Device:C","Capacitor_SMD:C_0805_2012Metric_Pad1.18x1.45mm_HandSolder","~"
"","","C10","100nF","Device:C","Capacitor_SMD:C_0805_2012Metric_Pad1.18x1.45mm_HandSolder","~"
"","","C11","10uF","Device:C","Capacitor_SMD:C_0805_2012Metric_Pad1.18x1.45mm_HandSolder","~"
"","","C12","100nF","Device:C","Capacitor_SMD:C_0805_2012Metric_Pad1.18x1.45mm_HandSolder","~"
"","","C13","100pF","Device:C","Capacitor_SMD:C_0805_2012Metric_Pad1.18x1.45mm_HandSolder","~"
"","","C14","100nF","Device:C","Capacitor_SMD:C_0805_2012Metric_Pad1.18x1.45mm_HandSolder","~"
"","","C15","100nF","Device:C","Capacitor_SMD:C_0805_2012Metric_Pad1.18x1.45mm_HandSolder","~"
"","","C16","10nF","Device:C","Capacitor_SMD:C_0805_2012Metric_Pad1.18x1.45mm_HandSolder","~"
"","","C17","10nF","Device:C","Capacitor_SMD:C_0805_2012Metric_Pad1.18x1.45mm_HandSolder","~"
"","","C18","10nF","Device:C","Capacitor_SMD:C_0805_2012Metric_Pad1.18x1.45mm_HandSolder","~"
"","","C19","10nF","Device:C","Capacitor_SMD:C_0805_2012Metric_Pad1.18x1.45mm_HandSolder","~"
"","","C20","1uF","Device:C","Capacitor_SMD:C_0805_2012Metric_Pad1.18x1.45mm_HandSolder","~"
"","","C21","100nF","Device:C","Capacitor_SMD:C_0805_2012Metric_Pad1.18x1.45mm_HandSolder","~"
"","","C22","100nF","Device:C","Capacitor_SMD:C_0805_2012Metric_Pad1.18x1.45mm_HandSolder","~"
"","","C23","100nF","Device:C","Capacitor_SMD:C_0805_2012Metric_Pad1.18x1.45mm_HandSolder","~"
"","","C24","1uF","Device:C","Capacitor_SMD:C_0805_2012Metric_Pad1.18x1.45mm_HandSolder","~"
"","","C25","10uF","Device:C","Capacitor_SMD:C_0805_2012Metric_Pad1.18x1.45mm_HandSolder","~"
"","","C26","100nF","Device:C","Capacitor_SMD:C_0805_2012Metric_Pad1.18x1.45mm_HandSolder","~"
"","","C27","33pF","Device:C","Capacitor_SMD:C_0805_2012Metric_Pad1.18x1.45mm_HandSolder","~"
"","","C28","10nF","Device:C","Capacitor_SMD:C_0805_2012Metric_Pad1.18x1.45mm_HandSolder","~"
"","","C29","10nF","Device:C","Capacitor_SMD:C_0805_2012Metric_Pad1.18x1.45mm_HandSolder","~"
"","","C30","10nF","Device:C","Capacitor_SMD:C_0805_2012Metric_Pad1.18x1.45mm_HandSolder","~"
"","","C31","100nF","Device:C","Capacitor_SMD:C_0805_2012Metric_Pad1.18x1.45mm_HandSolder","~"
"","","C32","10uF","Device:C","Capacitor_SMD:C_0805_2012Metric_Pad1.18x1.45mm_HandSolder","~"
"","","C33","100nF","Device:C","Capacitor_SMD:C_0805_2012Metric_Pad1.18x1.45mm_HandSolder","~"
"","","C34","100nF","Device:C","Capacitor_SMD:C_0805_2012Metric_Pad1.18x1.45mm_HandSolder","~"
"","","C35","10uF","Device:C","Capacitor_SMD:C_0805_2012Metric_Pad1.18x1.45mm_HandSolder","~"
"","","D1","MMBZ20VAL,215","Diode:MMBZxx","Package_TO_SOT_SMD:SOT-23","http://www.onsemi.com/pub/Collateral/MMBZ5V6ALT1-D.PDF"
"","","D2","VESD03C1-02V","Device:D_Zener","Diode_SMD:D_SOD-523","~"
"","","D4","1N4148","Diode:1N4148","Diode_SMD:D_SOD-123","https://assets.nexperia.com/documents/data-sheet/1N4148_1N4448.pdf"
"","","D5","LED","Device:LED","LED_SMD:LED_1206_3216Metric_Pad1.42x1.75mm_HandSolder","~"
"","","D6","VESD03C1-02V","Device:D_Zener","Diode_SMD:D_SOD-523","~"
"","","D7","VESD03C1-02V","Device:D_Zener","Diode_SMD:D_SOD-523","~"
"","","F1","PTC 100mA","Device:Polyfuse","Fuse:Fuse_1206_3216Metric_Pad1.42x1.75mm_HandSolder","~"
"","","F2","PTC 100mA","Device:Polyfuse","Fuse:Fuse_1206_3216Metric_Pad1.42x1.75mm_HandSolder","~"
"","","F3","PTC 100mA","Device:Polyfuse","Fuse:Fuse_1206_3216Metric_Pad1.42x1.75mm_HandSolder","~"
"","","F4","Polyfuse","Device:Polyfuse","Fuse:Fuse_1206_3216Metric_Pad1.42x1.75mm_HandSolder","~"
"","","J1","Conn_01x02_Female","Connector:Conn_01x02_Female","Connector_PinSocket_2.54mm:PinSocket_1x02_P2.54mm_Horizontal","~"
"","","J2","Conn_01x04_Male","Connector:Conn_01x04_Male","Connector_JST:JST_XH_B4B-XH-A_1x04_P2.50mm_Vertical","~"
"","","J3","USB_B_Micro","Connector:USB_B_Micro","mylib:USB_Micro-B_mine","~"
"","","J4","Conn_01x11_Male","Connector:Conn_01x11_Male","Connector_PinHeader_2.54mm:PinHeader_1x11_P2.54mm_Vertical","~"
"","","J5","Conn_01x02_Male","Connector:Conn_01x02_Male","Connector_PinHeader_2.54mm:PinHeader_1x02_P2.54mm_Vertical","~"
"","","J6","Conn_01x03_Male","Connector:Conn_01x03_Male","Connector_PinHeader_2.54mm:PinHeader_1x03_P2.54mm_Vertical","~"
"","","J9","Conn_01x02_Male","Connector:Conn_01x02_Male","Connector_PinHeader_2.54mm:PinHeader_1x02_P2.54mm_Vertical","~"
"","","JP1","Jumper_2_Bridged","Jumper:Jumper_2_Bridged","Jumper:SolderJumper-2_P1.3mm_Bridged_Pad1.0x1.5mm","~"
"","","L1","4.7uH Shld","Device:L_Ferrite","mylib:L_Coilcraft_LPS4018","~"
"","","Q1","DMN62D0UDW-13","Transistor_FET:FDG1024NZ","Package_TO_SOT_SMD:SOT-363_SC-70-6","https://www.onsemi.com/pub/Collateral/FDG1024NZ-D.pdf"
"","","Q2","DMN62D0UDW-13","Transistor_FET:FDG1024NZ","Package_TO_SOT_SMD:SOT-363_SC-70-6","https://www.onsemi.com/pub/Collateral/FDG1024NZ-D.pdf"
"","","R1","50mOhm precision","Device:R_Shunt","mylib:R_Shunt_Ohmite_LVK12_ALT","~"
"","","R2","0.5 Ohm precision","Device:R_Shunt","mylib:R_1206_3216Metric_4Wire","~"
"","","R3","5 Ohm precision","Device:R_Shunt","mylib:R_1206_3216Metric_4Wire","~"
"","","R4","45 Ohm precision","Device:R_Shunt","mylib:R_1206_3216Metric_4Wire","~"
"","","R5","10M","Device:R","Resistor_SMD:R_0805_2012Metric_Pad1.20x1.40mm_HandSolder","~"
"","","R6","100k","Device:R","Resistor_SMD:R_0805_2012Metric_Pad1.20x1.40mm_HandSolder","~"
"","","R7","1k","Device:R","Resistor_SMD:R_0805_2012Metric_Pad1.20x1.40mm_HandSolder","~"
"","","R8","10M","Device:R","Resistor_SMD:R_0805_2012Metric_Pad1.20x1.40mm_HandSolder","~"
"","","R9","100k","Device:R","Resistor_SMD:R_0805_2012Metric_Pad1.20x1.40mm_HandSolder","~"
"","","R10","220","Device:R","Resistor_SMD:R_0805_2012Metric_Pad1.20x1.40mm_HandSolder","~"
"","","R11","10k","Device:R","Resistor_SMD:R_0805_2012Metric_Pad1.20x1.40mm_HandSolder","~"
"","","R12","470","Device:R","Resistor_SMD:R_0805_2012Metric_Pad1.20x1.40mm_HandSolder","~"
"","","R13","4k7","Device:R","Resistor_SMD:R_0805_2012Metric_Pad1.20x1.40mm_HandSolder","~"
"","","R14","1M","Device:R","Resistor_SMD:R_0805_2012Metric_Pad1.20x1.40mm_HandSolder","~"
"","","R15","1M","Device:R","Resistor_SMD:R_0805_2012Metric_Pad1.20x1.40mm_HandSolder","~"
"","","R16","270","Device:R","Resistor_SMD:R_0805_2012Metric_Pad1.20x1.40mm_HandSolder","~"
"","","R17","270","Device:R","Resistor_SMD:R_0805_2012Metric_Pad1.20x1.40mm_HandSolder","~"
"","","R18","10M","Device:R","Resistor_SMD:R_0805_2012Metric_Pad1.20x1.40mm_HandSolder","~"
"","","R19","10M","Device:R","Resistor_SMD:R_0805_2012Metric_Pad1.20x1.40mm_HandSolder","~"
"","","R20","47","Device:R","Resistor_SMD:R_0805_2012Metric_Pad1.20x1.40mm_HandSolder","~"
"","","R21","47","Device:R","Resistor_SMD:R_0805_2012Metric_Pad1.20x1.40mm_HandSolder","~"
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
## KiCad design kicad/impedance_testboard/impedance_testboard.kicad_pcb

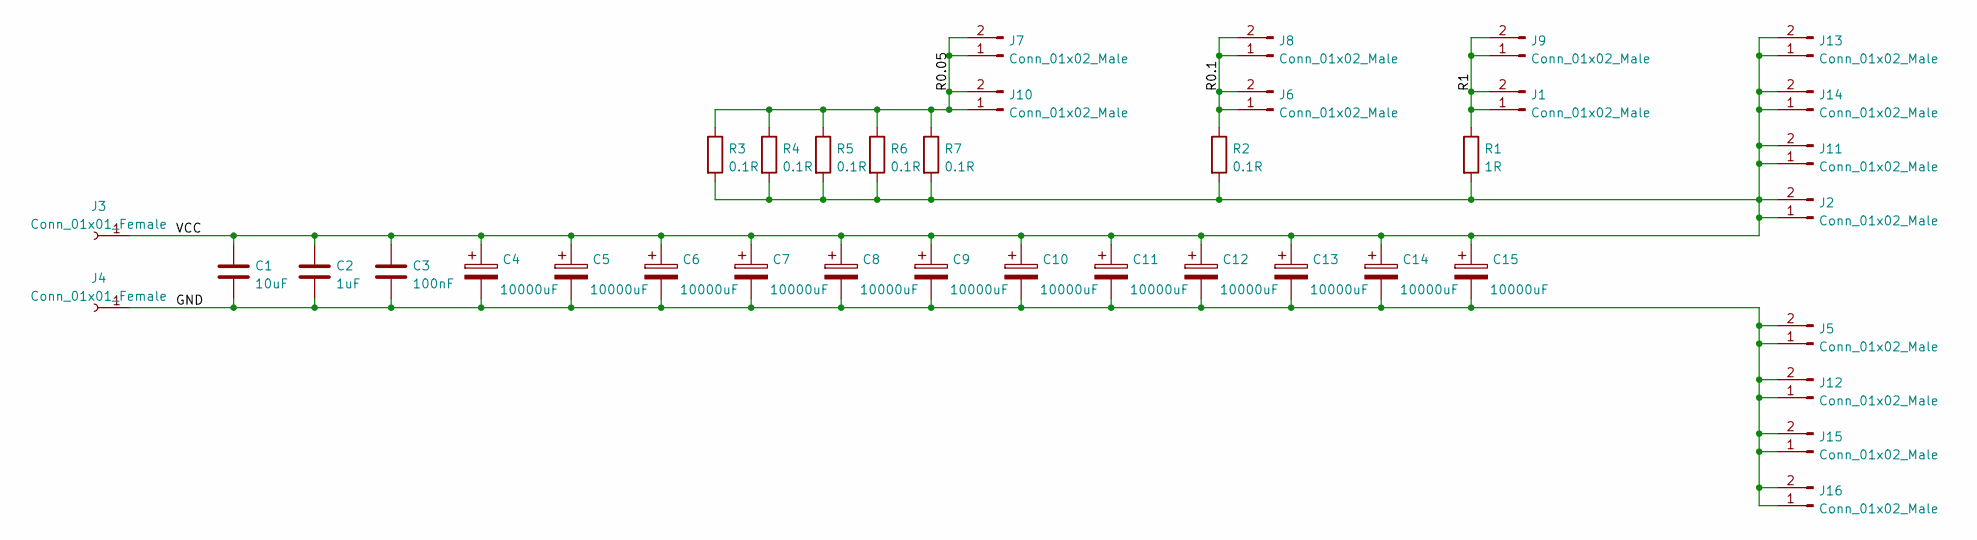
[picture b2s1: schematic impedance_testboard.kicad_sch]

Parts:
C1: 10uF; C_1206_3216Metric_Pad1.33x1.80mm_HandSolder
C2: 1uF; C_1206_3216Metric_Pad1.33x1.80mm_HandSolder
C3: 100nF; C_1206_3216Metric_Pad1.33x1.80mm_HandSolder
C4, C5, C6, C7, C8, C9, C10, C11, C12, C13, C14, C15: 10000uF; C_Radial_D18.0mm_H35.5mm_P7.50mm
J1, J2, J5, J6, J7, J8, J9, J10, J11, J12, J13, J14, J15, J16: Conn_01x02_Male; PinHeader_1x02_P2.54mm_Vertical
J3, J4: Conn_01x01_Female; PinHeader_1x01_P2.54mm_Horizontal
R1: 1R; R_1206_3216Metric_Pad1.30x1.75mm_HandSolder
R2, R3, R4, R5, R6, R7: 0.1R; R_1206_3216Metric_Pad1.30x1.75mm_HandSolder

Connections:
/GND: C1.2, C2.2, C3.2, C4.2, C5.2, C6.2, C7.2, C8.2, C9.2, C10.2, C11.2, C12.2, C13.2, C14.2, C15.2, J4.1, J5.1, J5.2, J12.1, J12.2, J15.1, J15.2, J16.1, J16.2
/R0.1: J6.1, J6.2, J8.1, J8.2, R2.1
/R0.05: J7.1, J7.2, J10.1, J10.2, R3.1, R4.1, R5.1, R6.1, R7.1
/R1: J1.1, J1.2, J9.1, J9.2, R1.1
/VCC: C1.1, C2.1, C3.1, C4.1, C5.1, C6.1, C7.1, C8.1, C9.1, C10.1, C11.1, C12.1, C13.1, C14.1, C15.1, J2.1, J2.2, J3.1, J11.1, J11.2, J13.1, J13.2, J14.1, J14.2, R1.2, R2.2, R3.2, R4.2, R5.2, R6.2, R7.2

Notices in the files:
batterymeter/batterymeter.ino:
Noto Mono is licensed under the SIL Open Font License (OFL)
